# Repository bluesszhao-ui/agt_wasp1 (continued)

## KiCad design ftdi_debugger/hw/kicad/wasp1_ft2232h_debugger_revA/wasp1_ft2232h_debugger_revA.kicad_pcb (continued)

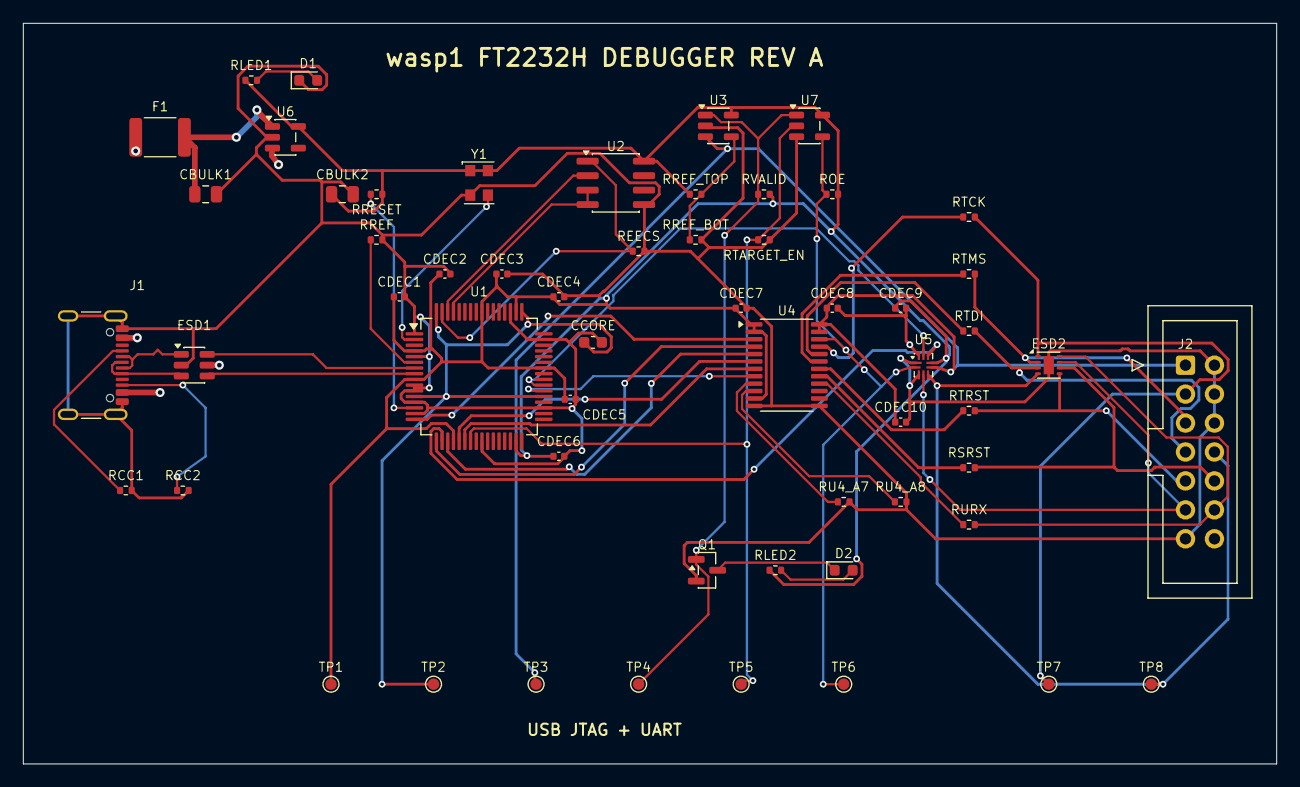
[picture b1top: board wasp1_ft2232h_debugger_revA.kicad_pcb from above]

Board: 4 copper layers, 110.0 x 65.0 mm, 57 parts (0 on the bottom side), 49 nets.

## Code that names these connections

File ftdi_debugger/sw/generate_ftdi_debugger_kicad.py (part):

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    ftdi_pins = [
        pin("1", "GND", "power_in", "L"), pin("2", "OSCI", "input", "L"), pin("3", "OSCO", "output", "L"), pin("4", "VPHY", "power_in", "L"),
        pin("5", "GND", "power_in", "L"), pin("6", "REF", "output", "L"), pin("7", "DM", "bidirectional", "L"), pin("8", "DP", "bidirectional", "L"),
        pin("9", "VPLL", "power_in", "L"), pin("10", "AGND", "power_in", "L"), pin("11", "GND", "power_in", "L"), pin("12", "VCORE", "power_in", "L"),
        pin("13", "TEST", "input", "L"), pin("14", "RESET_N", "input", "L"), pin("15", "GND", "power_in", "L"), pin("16", "ADBUS0", "bidirectional", "L"),
        pin("17", "ADBUS1", "bidirectional", "L"), pin("18", "ADBUS2", "bidirectional", "L"), pin("19", "ADBUS3", "bidirectional", "L"), pin("20", "VCCIOA", "power_in", "L"),
        pin("21", "ADBUS4", "bidirectional", "L"), pin("22", "ADBUS5", "bidirectional", "L"), pin("23", "ADBUS6", "bidirectional", "L"), pin("24", "ADBUS7", "bidirectional", "L"),
        pin("25", "GND", "power_in", "L"), pin("26", "ACBUS0", "bidirectional", "L"), pin("27", "ACBUS1", "bidirectional", "L"), pin("28", "ACBUS2", "bidirectional", "L"),
        pin("29", "ACBUS3", "bidirectional", "L"), pin("30", "ACBUS4", "bidirectional", "L"), pin("31", "VCCIOA", "power_in", "L"), pin("32", "ACBUS5", "bidirectional", "L"),
        pin("33", "ACBUS6", "bidirectional", "R"), pin("34", "ACBUS7", "bidirectional", "R"), pin("35", "GND", "power_in", "R"), pin("36", "SUSPEND_N", "output", "R"),
        pin("37", "VCORE", "power_in", "R"), pin("38", "BDBUS0", "bidirectional", "R"), pin("39", "BDBUS1", "bidirectional", "R"), pin("40", "BDBUS2", "bidirectional", "R"),
        pin("41", "BDBUS3", "bidirectional", "R"), pin("42", "VCCIOB", "power_in", "R"), pin("43", "BDBUS4", "bidirectional", "R"), pin("44", "BDBUS5", "bidirectional", "R"),
        pin("45", "BDBUS6", "bidirectional", "R"), pin("46", "BDBUS7", "bidirectional", "R"), pin("47", "GND", "power_in", "R"), pin("48", "BCBUS0", "bidirectional", "R"),
        pin("49", "VREGOUT", "power_out", "R"), pin("50", "VREGIN", "power_in", "R"), pin("51", "GND", "power_in", "R"), pin("52", "BCBUS1", "bidirectional", "R"),
        pin("53", "BCBUS2", "bidirectional", "R"), pin("54", "BCBUS3", "bidirectional", "R"), pin("55", "BCBUS4", "bidirectional", "R"), pin("56", "VCCIOB", "power_in", "R"),
        pin("57", "BCBUS5", "bidirectional", "R"), pin("58", "BCBUS6", "bidirectional", "R"), pin("59", "BCBUS7", "bidirectional", "R"), pin("60", "PWREN_N", "output", "R"),
        pin("61", "EEDATA", "bidirectional", "R"), pin("62", "EECLK", "output", "R"), pin("63", "EECS", "output", "R"), pin("64", "VCORE", "power_in", "R")]
    symbols["FTDI"] = make_symbol("FT2232HL", "U", "Package_QFP:LQFP-64_10x10mm_P0.5mm", "https://ftdichip.com/wp-content/uploads/2024/01/DS_FT2232H.pdf", ftdi_pins)
    symbols["EEPROM"] = make_symbol("93LC56BT-I-SN", "U", "Package_SO:SOIC-8_3.9x4.9mm_P1.27mm", "https://ww1.microchip.com/downloads/en/DeviceDoc/21794G.pdf", [
        pin("1", "CS", "input", "L"), pin("2", "CLK", "input", "L"), pin("3", "DI", "input", "L"), pin("4", "DO", "tri_state", "L"),
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
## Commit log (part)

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2026-06-10 Initial wasp1 architecture scaffold
2026-06-10 Add common RTL foundation and bus specs
2026-06-10 Implement AHB address decoder
2026-06-10 Strengthen AHB decoder verification coverage
2026-06-10 Add agent contribution guide
2026-06-10 Add project foundation documents
2026-06-10 Implement and verify AHB default slave
2026-06-10 Document simulation timing policy
2026-06-10 Align default slave with clocked AHB interface
2026-06-10 Implement and verify AHB slave mux
2026-06-11 Implement and verify AHB 2-master arbiter
2026-06-11 Add bus submodule block diagrams
2026-06-11 Integrate and verify initial AHB fabric
2026-06-11 Implement and verify AHB SRAM slave
2026-06-11 Add IC and Virtex-7 target policy
2026-06-11 Implement and verify AHB OTP slave
2026-06-11 Implement and verify AHB timer
2026-06-11 Implement and verify AHB GPIO
2026-06-11 Implement and verify AHB UART
2026-06-11 Implement and verify AHB DMA
2026-06-11 Add module spec documentation
2026-06-11 Implement and verify AHB interrupt controller
2026-06-11 Implement and verify core ALU
2026-06-11 Implement and verify core register file
2026-06-11 Implement and verify core decoder
2026-06-11 Implement and verify core branch helper
2026-06-11 Implement and verify core CSR file
2026-06-11 Implement and verify core LSU helper
2026-06-11 Implement and verify core trap helper
2026-06-11 Document core RTL and verification intent
2026-06-12 Implement and verify core hazard helper
2026-06-12 Implement and verify core writeback helper
2026-06-12 Implement and verify core pipeline skeleton
2026-06-12 Document sequential state requirements
2026-06-12 Add PNG state diagrams
2026-06-12 Add detailed L3 state diagrams
2026-06-12 Refine DMA L3 state diagrams
2026-06-12 Implement and verify core integer datapath
2026-06-13 Integrate core branch redirects
2026-06-13 Integrate core load store datapath
2026-06-13 Integrate core CSR trap interrupt path
2026-06-13 Integrate core load use hazard control
2026-06-15 Wrap datapath in core top
2026-06-15 Implement frontend PC control
2026-06-15 Implement frontend fetch control
2026-06-17 Clarify diagram timing domains
2026-06-17 Annotate prior diagrams with timing classes
2026-06-17 Implement frontend instruction buffer
2026-06-17 Integrate frontend top
2026-06-17 Implement icache tag store
2026-06-17 Split mixed timing blocks in diagrams
2026-06-17 Implement icache data store
2026-06-17 Implement icache refill sequencer
2026-06-17 Implement icache control path
2026-06-17 Integrate icache top
2026-06-17 Implement dcache tag leaf
2026-06-17 Implement dcache data store
2026-06-17 Implement dcache refill sequencer
2026-06-17 Implement dcache store sequencer
2026-06-17 Implement dcache control sequencer
2026-06-18 Integrate top-level dcache
2026-06-18 Document module decks and diagram color policy
2026-06-18 Refactor core fetch to frontend stream
2026-06-18 Add core data valid-ready handshake
2026-06-23 Integrate complete CPU tile
2026-06-23 Add verified debug DMI register block
2026-06-24 Add verified debug halt controller
2026-06-24 Add verified debug GPR access sequencer
2026-06-24 Add verified abstract GPR command controller
2026-06-24 Adopt OmniGraffle diagram policy
2026-06-24 Add verified core debug hooks
2026-06-26 Add WDG I2C and initial SoC top
2026-06-26 Add early module editable block diagrams
2026-06-26 Add UART DMA INTC editable block diagrams
2026-06-26 Add frontend editable block diagrams
2026-06-29 Add core leaf editable block diagrams
2026-06-29 Add core CSR trap LSU editable block diagrams
2026-06-29 Add core integration editable block diagrams
2026-06-29 Add icache editable block diagrams
2026-06-29 Add dcache editable block diagrams
2026-06-29 Add bus submodule editable block diagrams
2026-06-29 Add UART leaf editable block diagrams
2026-06-29 Add debug editable diagrams
2026-06-29 Add tile editable diagram
2026-06-29 Add debug design presentation
2026-06-30 Add i2c design presentation
2026-06-30 Add watchdog design presentation
2026-06-30 Add wasp1 top design presentation
2026-06-30 Update project status documentation
2026-06-30 Add llvm_s1 stage1 BSP skeleton
2026-06-30 Add llvm_s1 toolchain smoke tests
2026-06-30 Add llvm_s1 toolchain environment setup
